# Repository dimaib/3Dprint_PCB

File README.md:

# 3D printer Dual
## Description
A board for controlling all parts of a dual-extruder 3D printer.
- Allows you to control 6 stepper motors
- Table heating 110-230V
- Chamber heating 110-230V
- Heat control of two extruders
- Connection of various limit switches
- Connecting the LCD display
- Printer management via web interface via TCP/IP
>This board is controlled by [RepRapFirmware](https://reprap.org/wiki/RepRap_Firmware) ([GitHub](https://github.com/reprappro/RepRapFirmware))

RepRapFirmware has been optimized and redesigned for the STM32F407VGT controller architecture

## Tools and softwire
- The printed circuit board and circuit diagram of the device are created in [KiCad](https://www.kicad.org/)
- 3D models for PCB components were created in SOLIDWORKS
- Firmware edit in [Atollic TrueSTUDIO for STM32](https://www.st.com/en/development-tools/truestudio.html) in C languages
## Main view PCB

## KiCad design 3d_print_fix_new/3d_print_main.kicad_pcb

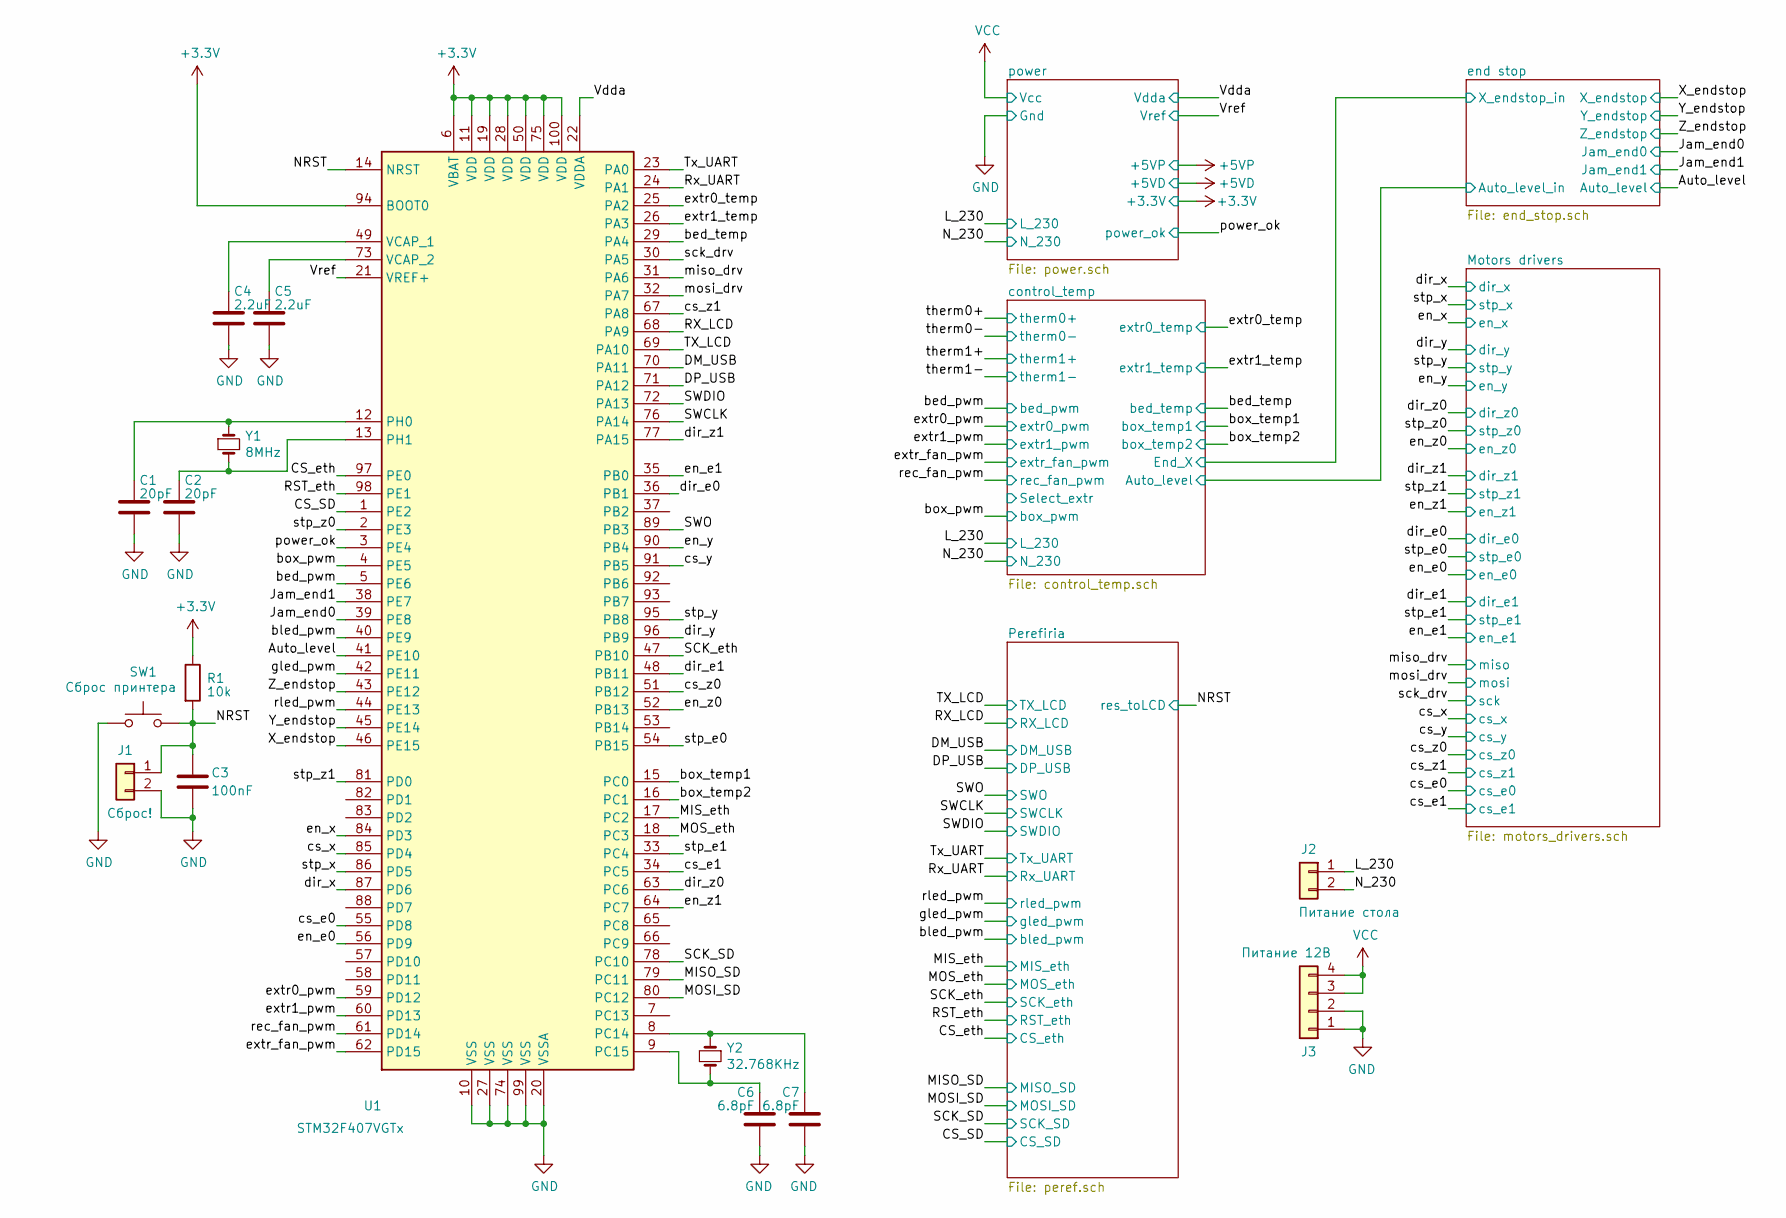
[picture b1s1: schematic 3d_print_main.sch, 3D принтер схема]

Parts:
C1, C2: 20pF; C_0603_1608Metric
C3: 100nF; C_0603_1608Metric
C4, C5: 2.2uF; C_0603_1608Metric
C6, C7: 6.8pF; C_0603_1608Metric
J1: Сброс!; PhoenixContact_MCV_1,5_2-G-3.5_1x02_P3.50mm_Vertical
J2: Питание стола; PhoenixContact_MCV_1,5_2-G-3.5_1x02_P3.50mm_Vertical
J3: Питание 12В; PhoenixContact_MCV_1,5_4-G-3.5_1x04_P3.50mm_Vertical
R1: 10k; R_0603_1608Metric
SW1: Сброс принтера; SW_SPST_PTS645
U1: STM32F407VGTx; LQFP-100_14x14mm_P0.5mm
Y1: 8MHz; Crystal_SMD_5032-2Pin_5.0x3.2mm_HandSoldering
Y2: 32.768KHz; Crystal_SMD_3215-2Pin_3.2x1.5mm

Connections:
/Auto_level: U1.41 (PE10); also elsewhere on the board
/CS_SD: U1.1 (PE2); also elsewhere on the board
/CS_eth: U1.97 (PE0); also elsewhere on the board
/DM_USB: U1.70 (PA11); also elsewhere on the board
/DP_USB: U1.71 (PA12); also elsewhere on the board
/Jam_end0: U1.39 (PE8); also elsewhere on the board
/Jam_end1: U1.38 (PE7); also elsewhere on the board
/L_230: J2.1; also elsewhere on the board
/MISO_SD: U1.79 (PC11); also elsewhere on the board
/MIS_eth: U1.17 (PC2); also elsewhere on the board
/MOSI_SD: U1.80 (PC12); also elsewhere on the board
/MOS_eth: U1.18 (PC3); also elsewhere on the board
/N_230: J2.2; also elsewhere on the board
/RST_eth: U1.98 (PE1); also elsewhere on the board
/RX_LCD: U1.68 (PA9); also elsewhere on the board
/Rx_UART: U1.24 (PA1); also elsewhere on the board
/SCK_SD: U1.78 (PC10); also elsewhere on the board
/SCK_eth: U1.47 (PB10); also elsewhere on the board
/SWCLK: U1.76 (PA14); also elsewhere on the board
/SWDIO: U1.72 (PA13); also elsewhere on the board
/TX_LCD: U1.69 (PA10); also elsewhere on the board
/Tx_UART: U1.23 (PA0); also elsewhere on the board
/Vdda: U1.22 (VDDA); also elsewhere on the board
/Vref: U1.21 (VREF+); also elsewhere on the board
/X_endstop: U1.46 (PE15); also elsewhere on the board
/Y_endstop: U1.45 (PE14); also elsewhere on the board
/Z_endstop: U1.43 (PE12); also elsewhere on the board
/bed_pwm: U1.5 (PE6); also elsewhere on the board
/bed_temp: U1.29 (PA4); also elsewhere on the board
/bled_pwm: U1.40 (PE9); also elsewhere on the board
/box_pwm: U1.4 (PE5); also elsewhere on the board
/box_temp1: U1.15 (PC0); also elsewhere on the board
/box_temp2: U1.16 (PC1); also elsewhere on the board
/cs_e0: U1.55 (PD8); also elsewhere on the board
/cs_e1: U1.34 (PC5); also elsewhere on the board
/cs_x: U1.85 (PD4); also elsewhere on the board
/cs_y: U1.91 (PB5); also elsewhere on the board
/cs_z0: U1.51 (PB12); also elsewhere on the board
/cs_z1: U1.67 (PA8); also elsewhere on the board
/dir_e0: U1.36 (PB1); also elsewhere on the board
/dir_e1: U1.48 (PB11); also elsewhere on the board
/dir_x: U1.87 (PD6); also elsewhere on the board
/dir_y: U1.96 (PB9); also elsewhere on the board
/dir_z0: U1.63 (PC6); also elsewhere on the board
/dir_z1: U1.77 (PA15); also elsewhere on the board
/en_e0: U1.56 (PD9); also elsewhere on the board
/en_e1: U1.35 (PB0); also elsewhere on the board
/en_x: U1.84 (PD3); also elsewhere on the board
/en_y: U1.90 (PB4); also elsewhere on the board
/en_z0: U1.52 (PB13); also elsewhere on the board
/en_z1: U1.64 (PC7); also elsewhere on the board
/extr0_pwm: U1.59 (PD12); also elsewhere on the board
/extr0_temp: U1.25 (PA2); also elsewhere on the board
/extr1_pwm: U1.60 (PD13); also elsewhere on the board
/extr1_temp: U1.26 (PA3); also elsewhere on the board
/extr_fan_pwm: U1.62 (PD15); also elsewhere on the board
/gled_pwm: U1.42 (PE11); also elsewhere on the board
/miso_drv: U1.31 (PA6); also elsewhere on the board
/mosi_drv: U1.32 (PA7); also elsewhere on the board
/power_ok: U1.3 (PE4); also elsewhere on the board
/rec_fan_pwm: U1.61 (PD14); also elsewhere on the board
/rled_pwm: U1.44 (PE13); also elsewhere on the board
/sck_drv: U1.30 (PA5); also elsewhere on the board
/stp_e0: U1.54 (PB15); also elsewhere on the board
/stp_e1: U1.33 (PC4); also elsewhere on the board
/stp_x: U1.86 (PD5); also elsewhere on the board
/stp_y: U1.95 (PB8); also elsewhere on the board
/stp_z0: U1.2 (PE3); also elsewhere on the board
/stp_z1: U1.81 (PD0); also elsewhere on the board
unnamed: C4.1, U1.49 (VCAP_1)
unnamed: C5.1, U1.73 (VCAP_2)
unnamed: C6.1, U1.9 (PC15), Y2.2
unnamed: C7.1, U1.8 (PC14), Y2.1
VCC: J3.3, J3.4; also elsewhere on the board

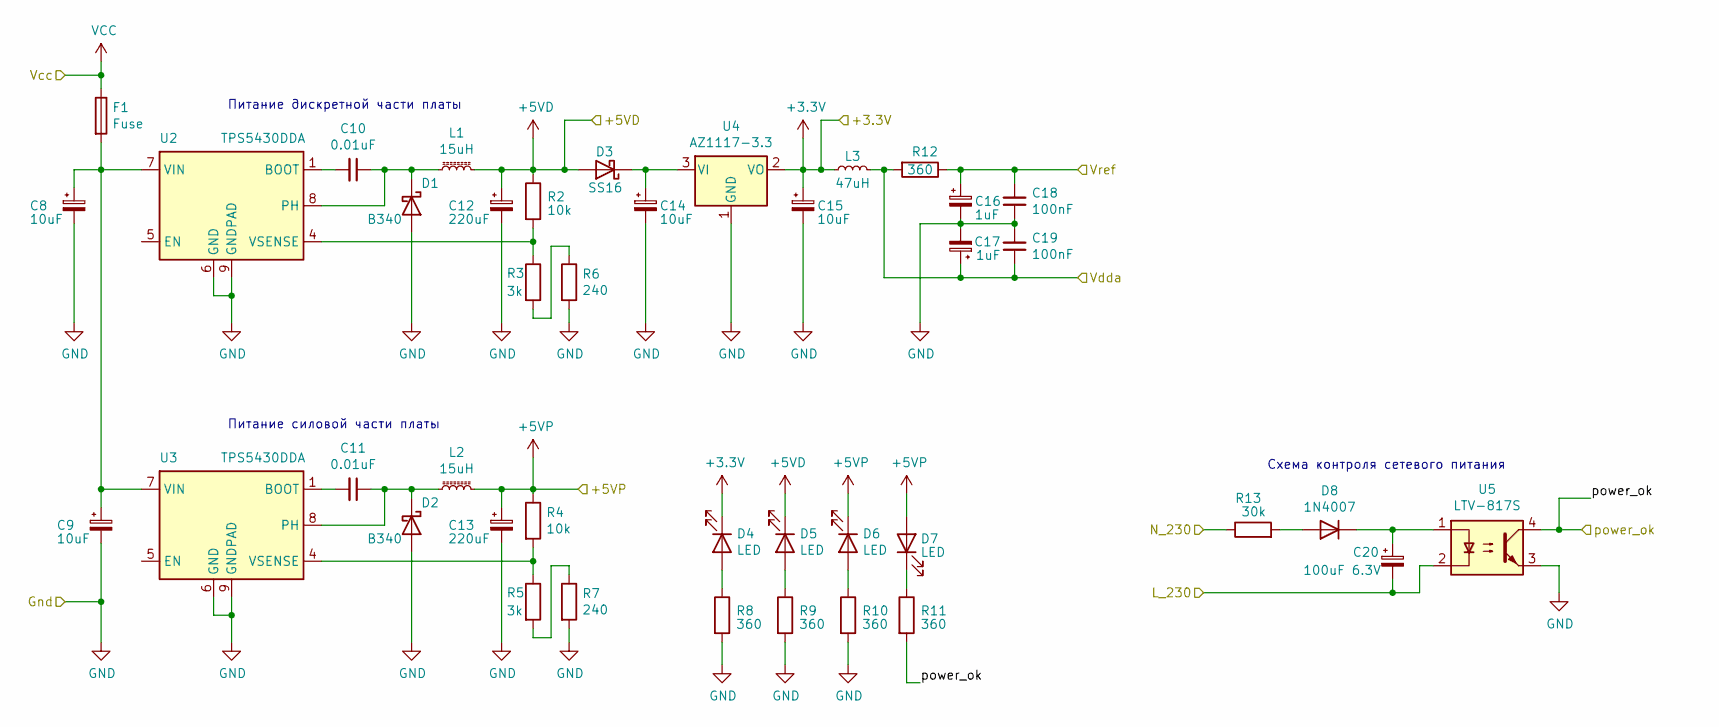
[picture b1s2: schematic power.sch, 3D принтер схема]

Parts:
C8, C9: 10uF; CP_EIA-6032-28_Kemet-C
C10, C11: 0.01uF; C_0603_1608Metric
C12, C13: 220uF; CP_Elec_6.3x7.7
C14, C15: 10uF; CP_EIA-3216-18_Kemet-A
C16, C17: 1uF; CP_EIA-3216-18_Kemet-A
C18, C19: 100nF; C_0603_1608Metric
C20: 100uF 6.3V; CP_EIA-3528-21_Kemet-B
D1, D2: B340; D_SMA
D3: SS16; D_SMA
D4, D5, D6, D7: LED; LED_1206_3216Metric
D8: 1N4007; D_DO-41_SOD81_P7.62mm_Horizontal
F1: Fuse; MF-SM250_Fuse
L1, L2: 15uH; L_10.4x10.4_H4.8
L3: 47uH; L_0805_2012Metric
R2, R4: 10k; R_0603_1608Metric
R3, R5: 3k; R_0603_1608Metric
R6, R7: 240; R_0603_1608Metric
R8, R9, R10, R11, R12: 360; R_0603_1608Metric
R13: 30k; R_2512_6332Metric
U2, U3: TPS5430DDA; TI_SO-PowerPAD-8_ThermalVias
U4: AZ1117-3.3; SOT-223-3_TabPin2
U5: LTV-817S; SMDIP-4_W9.53mm

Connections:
/L_230: C20.2, U5.2; also elsewhere on the board
/N_230: R13.1; also elsewhere on the board
/Vdda: C17.1, C19.1, L3.2, R12.2; also elsewhere on the board
/Vref: C16.1, C18.2, R12.1; also elsewhere on the board
/power_ok: R11.2, U5.4; also elsewhere on the board
unnamed: C8.1, C9.1, F1.2, U2.7 (VIN), U3.7 (VIN)
unnamed: C10.1, D1.1 (K), L1.1, U2.8 (PH)
unnamed: C10.2, U2.1 (BOOT)
unnamed: C11.2, U3.1 (BOOT)
unnamed: C14.1, D3.1 (K), U4.3 (VI)
unnamed: C20.1, D8.2 (K), U5.1
unnamed: D4.2 (A), R8.1
unnamed: D5.2 (A), R9.1
unnamed: D7.1 (K), R11.1
unnamed: D8.1 (A), R13.2
unnamed: R2.2, R3.1, U2.4 (VSENSE)
unnamed: R3.2, R6.1
VCC: F1.1; also elsewhere on the board

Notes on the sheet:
Питание дискретной части платы
Питание силовой части платы
Схема контроля сетевого питания

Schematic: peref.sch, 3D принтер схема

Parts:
C1, C2: 10uF; C_0603_1608Metric
C3, C22, C23: 1uF; C_0603_1608Metric
C21: 10uF; CP_EIA-3216-18_Kemet-A
D2, D9: BAS321; D_SOD-323_HandSoldering
D6: Зелёный; LED_0603_1608Metric_Castellated
D10: SP0503; SOT-143
D11: w5500_module
J4, J5, J7, J12, J14, J16, J18, J20, J21: Conn_01x01; PinHeader_1x01_P2.54mm_Vertical
J6, J8, J11, J13, J15, J17, J19, J45, J46: Conn_01x01; MountingHole_3.2mm_M3_Pad_Via
J9: На монитор; IDC-Header_2x04_P2.54mm_Vertical
J10: LMT01 датчик т; PinHeader_1x01_P2.54mm_Vertical
J22: ST-Link; ZH_Conn_04x01
J23: USB_B_Mini; USB_Micro-B_Molex-105017-0001
J25: Подключение RGB ленты; PhoenixContact_MCV_1,5_3-G-3.5_1x03_P3.50mm_Vertical
Q1: BC817; SOT-23
Q2, Q3: IRLML2060; SOT-23
R4, R15, R18, R19, R20, R25, R26, R59, R60, R61: 10k; R_0603_1608Metric
R5, R7: 50k; R_0603_1608Metric
R10: 150k; R_0603_1608Metric
R14: 360; R_0603_1608Metric
R16, R17: 22; R_0603_1608Metric
R22, R23: 100; R_0603_1608Metric
SW1: Сброс принтера; SW_SPST_PTS645
SW2: Сброс по UART; SW_DIP_SPSTx01_Piano_10.8x4.1mm_W7.62mm_P2.54mm
U3, U11: 74LVC2G14; SOT-23-6
U6: USBLC6-2SC6; SOT-23-6
U7: MicroSD_SPI_CD; GCT-MEM2055-00-190-01-A
U8: CP2102N; QFN-28-1EP_5x5mm_P0.5mm_EP3.35x3.35mm
U12: TPS73018DBV; SOT-23-5

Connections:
/CS_SD: U7.2 (~CS); also elsewhere on the board
/CS_eth: D11.5 (SCN); also elsewhere on the board
/DM_USB: R17.1; also elsewhere on the board
/DP_USB: R16.1; also elsewhere on the board
/MISO_SD: U7.7 (DO); also elsewhere on the board
/MIS_eth: D11.7 (MISO); also elsewhere on the board
/MOSI_SD: U7.3 (DI); also elsewhere on the board
/MOS_eth: D11.3 (MOSI); also elsewhere on the board
/Perefiria/blue_led: J25.4; also elsewhere on the board
/Perefiria/green_led: J25.3, Q3.3 (D), R26.2
/Perefiria/red_led: J25.2, Q2.3 (D), R25.2
/RST_eth: D11.8 (RST); also elsewhere on the board
/RX_LCD: J9.6; also elsewhere on the board
/Rx_UART: U8.26 (TXD); also elsewhere on the board
/SCK_SD: U7.5 (SCLK); also elsewhere on the board
/SCK_eth: D11.4 (SCK); also elsewhere on the board
/SWCLK: J22.3; also elsewhere on the board
/SWDIO: J22.5; also elsewhere on the board
/TX_LCD: J9.8; also elsewhere on the board
/Tx_UART: U8.25 (RXD); also elsewhere on the board
/gled_pwm: R20.1, R23.2; also elsewhere on the board
/rled_pwm: R19.1, R22.2; also elsewhere on the board
unnamed 86: C23.1; also elsewhere on the board
unnamed: C23.2, U8.28 (~DTR)
unnamed: D9.1 (A), J23.1 (VBUS)
unnamed: D10.3 (K), J23.2 (D-), U8.5 (D-)
unnamed: D10.4 (K), J23.3 (D+), U8.4 (D+)
unnamed: J9.2, U6.1 (IO1)
unnamed: J9.4, U6.3 (IO2)
unnamed: J9.10, R14.1
unnamed: Q1.1 (B), R14.2, R15.1
unnamed: Q2.1 (G), R22.1
unnamed: Q3.1 (G), R23.1
unnamed: R16.2, U6.6 (IO1)
unnamed: R17.2, U6.4 (IO2)
unnamed: R18.2, U8.9 (~RSTb)
unnamed: R59.1, R60.1
VCC: J25.1, R25.1, R26.1; also elsewhere on the board

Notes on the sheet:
USB-UART debug
Защита USB от ЭМП
Для осциллографа
Отверстия для крепежа M3
Схема сброса

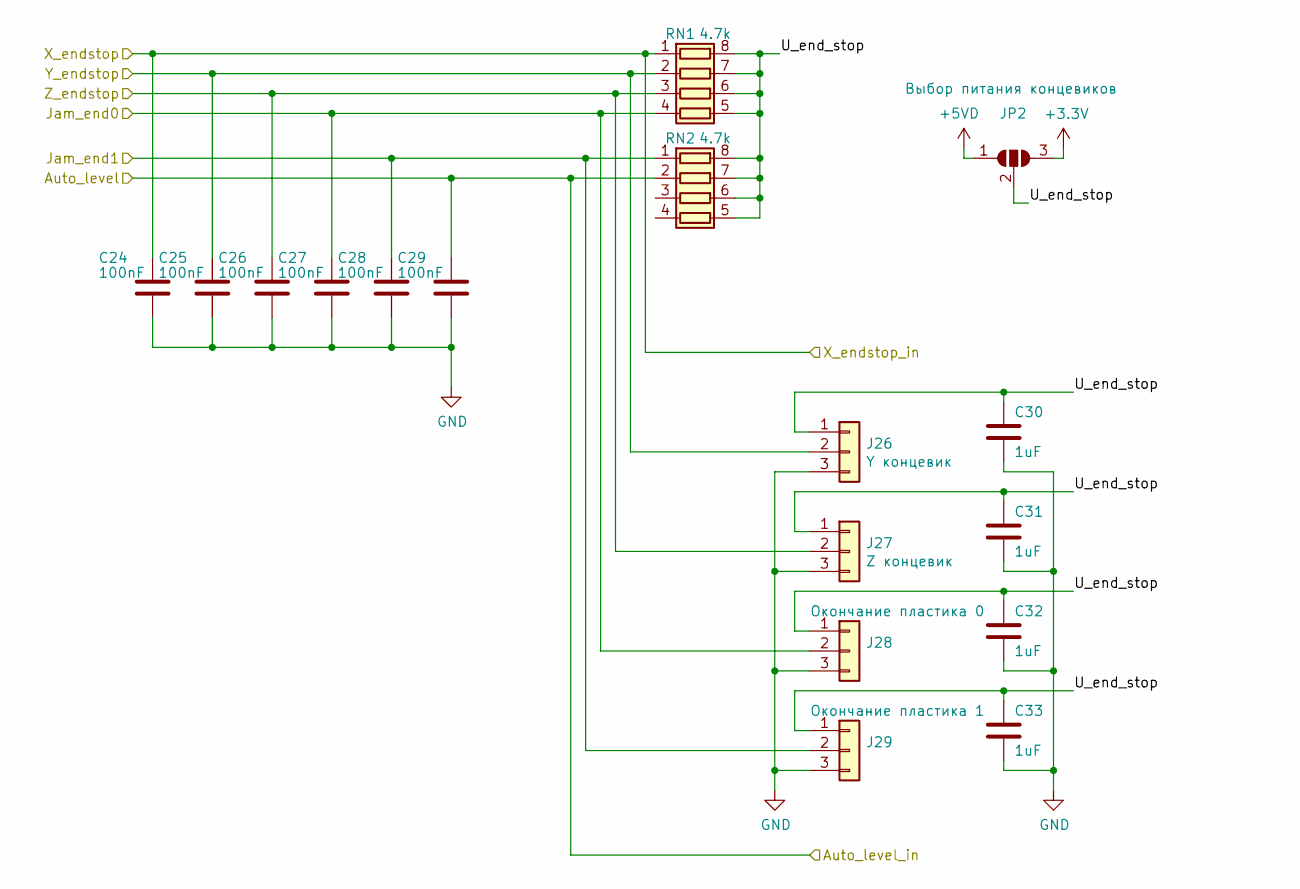
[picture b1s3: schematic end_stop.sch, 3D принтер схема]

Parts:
C24, C25, C26, C27, C28, C29: 100nF; C_0603_1608Metric
C30, C31, C32, C33: 1uF; C_0603_1608Metric
J26: Y концевик; PhoenixContact_MCV_1,5_3-G-3.5_1x03_P3.50mm_Vertical
J27: Z концевик; PhoenixContact_MCV_1,5_3-G-3.5_1x03_P3.50mm_Vertical
J28: Окончание пластика 0; PhoenixContact_MCV_1,5_3-G-3.5_1x03_P3.50mm_Vertical
J29: Окончание пластика 1; PhoenixContact_MCV_1,5_3-G-3.5_1x03_P3.50mm_Vertical
JP2: Выбор питания концевиков; SolderJumper-3_P1.3mm_Bridged2Bar12_RoundedPad1.0x1.5mm_Num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
RN1, RN2: 4.7k; R_Array_Convex_4x0603

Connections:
/Auto_level: C29.1, RN2.2 (R2.1); also elsewhere on the board
/Jam_end0: C27.1, J28.2, RN1.4 (R4.1); also elsewhere on the board
/Jam_end1: C28.1, J29.2, RN2.1 (R1.1); also elsewhere on the board
/X_endstop: C24.1, RN1.1 (R1.1); also elsewhere on the board
/Y_endstop: C25.1, J26.2, RN1.2 (R2.1); also elsewhere on the board
/Z_endstop: C26.1, J27.2, RN1.3 (R3.1); also elsewhere on the board
/end stop/U_end_stop: C30.1, C31.1, C32.1, C33.1, J26.1, J27.1, J28.1, J29.1, JP2.2 (C), RN1.5 (R4.2), RN1.6 (R3.2), RN1.7 (R2.2), RN1.8 (R1.2), RN2.5 (R4.2), RN2.6 (R3.2), RN2.7 (R2.2), RN2.8 (R1.2)

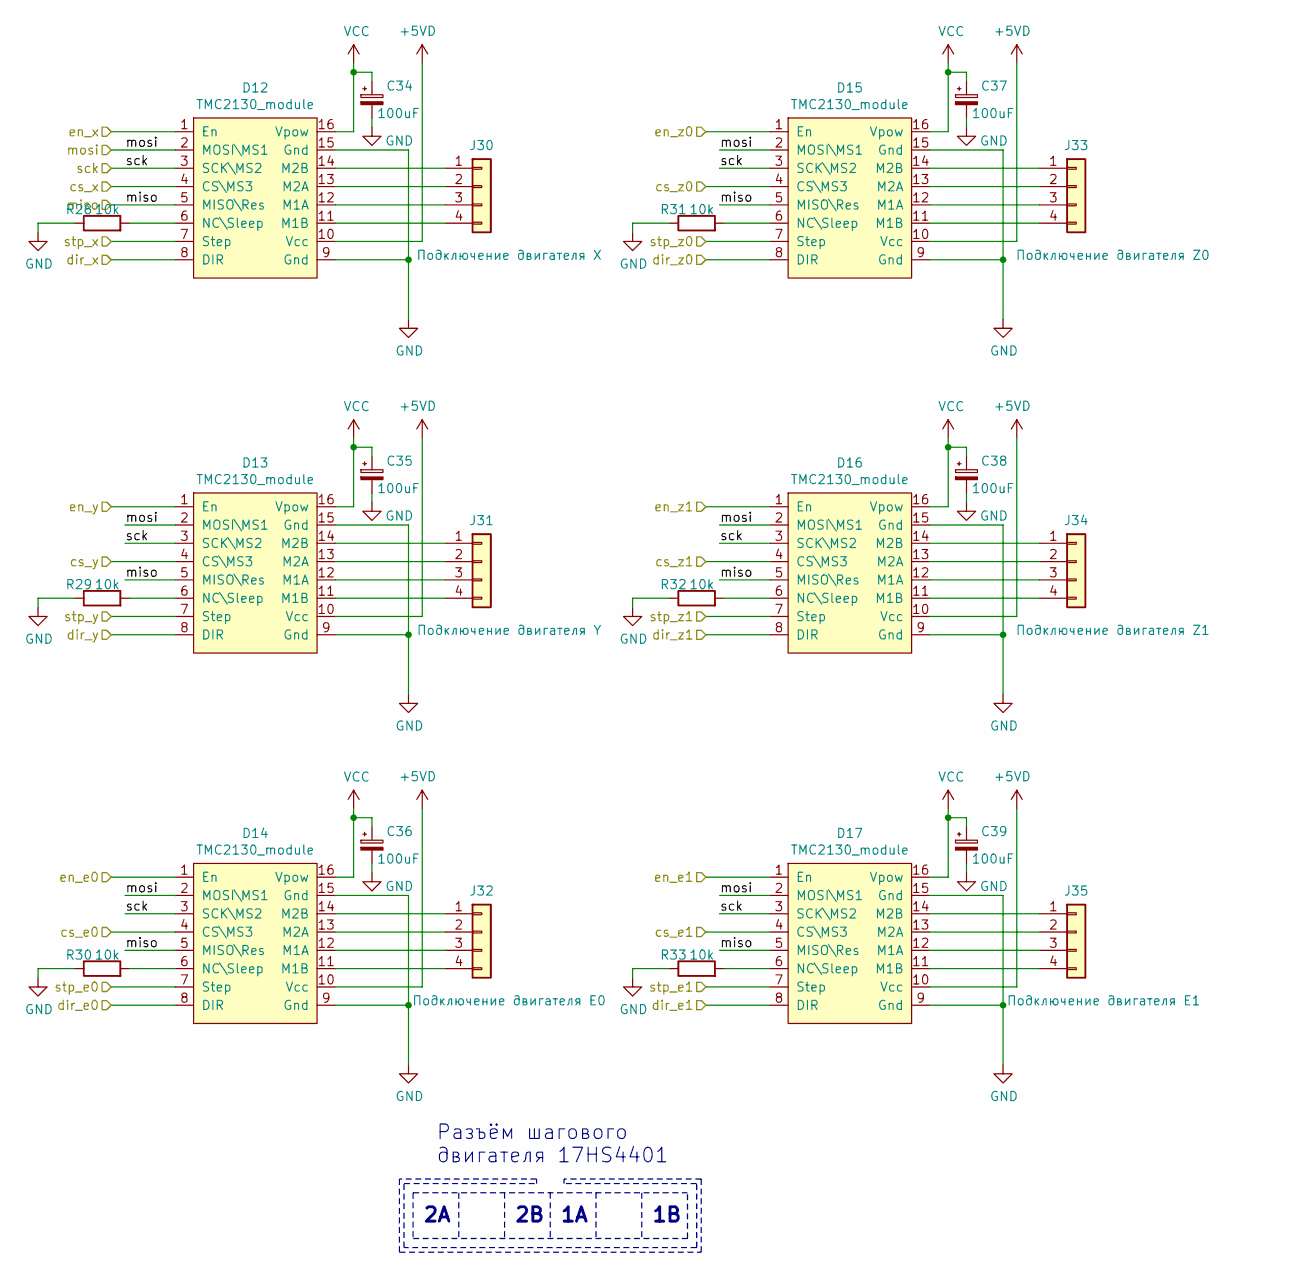
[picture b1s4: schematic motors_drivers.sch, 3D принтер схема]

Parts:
C34, C35, C36, C37, C38, C39: 100uF; CP_Elec_6.3x7.7
D12, D13, D14, D15, D16, D17: TMC2130_module; TMC2130_Module
J30: Подключение двигателя X; PhoenixContact_MCV_1,5_4-G-3.5_1x04_P3.50mm_Vertical
J31: Подключение двигателя Y; PhoenixContact_MCV_1,5_4-G-3.5_1x04_P3.50mm_Vertical
J32: Подключение двигателя E0; PhoenixContact_MCV_1,5_4-G-3.5_1x04_P3.50mm_Vertical
J33: Подключение двигателя Z0; PhoenixContact_MCV_1,5_4-G-3.5_1x04_P3.50mm_Vertical
J34: Подключение двигателя Z1; PhoenixContact_MCV_1,5_4-G-3.5_1x04_P3.50mm_Vertical
J35: Подключение двигателя E1; PhoenixContact_MCV_1,5_4-G-3.5_1x04_P3.50mm_Vertical
R28, R29, R30, R31, R32, R33: 10k; R_0603_1608Metric

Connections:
/cs_e0: D14.4 (CS\MS3); also elsewhere on the board
/cs_e1: D17.4 (CS\MS3); also elsewhere on the board
/cs_x: D12.4 (CS\MS3); also elsewhere on the board
/cs_y: D13.4 (CS\MS3); also elsewhere on the board
/cs_z0: D15.4 (CS\MS3); also elsewhere on the board
/cs_z1: D16.4 (CS\MS3); also elsewhere on the board
/dir_e0: D14.8 (DIR); also elsewhere on the board
/dir_e1: D17.8 (DIR); also elsewhere on the board
/dir_x: D12.8 (DIR); also elsewhere on the board
/dir_y: D13.8 (DIR); also elsewhere on the board
/dir_z0: D15.8 (DIR); also elsewhere on the board
/dir_z1: D16.8 (DIR); also elsewhere on the board
/en_e0: D14.1 (En); also elsewhere on the board
/en_e1: D17.1 (En); also elsewhere on the board
/en_x: D12.1 (En); also elsewhere on the board
/en_y: D13.1 (En); also elsewhere on the board
/en_z0: D15.1 (En); also elsewhere on the board
/en_z1: D16.1 (En); also elsewhere on the board
/miso_drv: D12.5 (MISO\Res), D13.5 (MISO\Res), D14.5 (MISO\Res), D15.5 (MISO\Res), D16.5 (MISO\Res), D17.5 (MISO\Res); also elsewhere on the board
/mosi_drv: D12.2 (MOSI\MS1), D13.2 (MOSI\MS1), D14.2 (MOSI\MS1), D15.2 (MOSI\MS1), D16.2 (MOSI\MS1), D17.2 (MOSI\MS1); also elsewhere on the board
/sck_drv: D12.3 (SCK\MS2), D13.3 (SCK\MS2), D14.3 (SCK\MS2), D15.3 (SCK\MS2), D16.3 (SCK\MS2), D17.3 (SCK\MS2); also elsewhere on the board
/stp_e0: D14.7 (Step); also elsewhere on the board
/stp_e1: D17.7 (Step); also elsewhere on the board
/stp_x: D12.7 (Step); also elsewhere on the board
/stp_y: D13.7 (Step); also elsewhere on the board
/stp_z0: D15.7 (Step); also elsewhere on the board
/stp_z1: D16.7 (Step); also elsewhere on the board
unnamed: D12.6 (NC\Sleep), R28.2
unnamed: D12.11 (M1B), J30.4
unnamed: D12.12 (M1A), J30.3
unnamed: D12.13 (M2A), J30.2
unnamed: D12.14 (M2B), J30.1
unnamed: D13.6 (NC\Sleep), R29.2
unnamed: D13.11 (M1B), J31.4
unnamed: D13.12 (M1A), J31.3
unnamed: D13.13 (M2A), J31.2
unnamed: D13.14 (M2B), J31.1
unnamed: D14.6 (NC\Sleep), R30.2
unnamed: D14.11 (M1B), J32.4
unnamed: D14.12 (M1A), J32.3
unnamed: D14.13 (M2A), J32.2
unnamed: D14.14 (M2B), J32.1
unnamed: D15.6 (NC\Sleep), R31.2
unnamed: D15.11 (M1B), J33.4
unnamed: D15.12 (M1A), J33.3
unnamed: D15.13 (M2A), J33.2
unnamed: D15.14 (M2B), J33.1
unnamed: D16.6 (NC\Sleep), R32.2
unnamed: D16.11 (M1B), J34.4
unnamed: D16.12 (M1A), J34.3
unnamed: D16.13 (M2A), J34.2
unnamed: D16.14 (M2B), J34.1
unnamed: D17.6 (NC\Sleep), R33.2
unnamed: D17.11 (M1B), J35.4
unnamed: D17.12 (M1A), J35.3
unnamed: D17.13 (M2A), J35.2
unnamed: D17.14 (M2B), J35.1
VCC: C34.1, C35.1, C36.1, C37.1, C38.1, C39.1, D12.16 (Vpow), D13.16 (Vpow), D14.16 (Vpow), D15.16 (Vpow), D16.16 (Vpow), D17.16 (Vpow); also elsewhere on the board

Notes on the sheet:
Разъём шагового двигателя 17HS4401

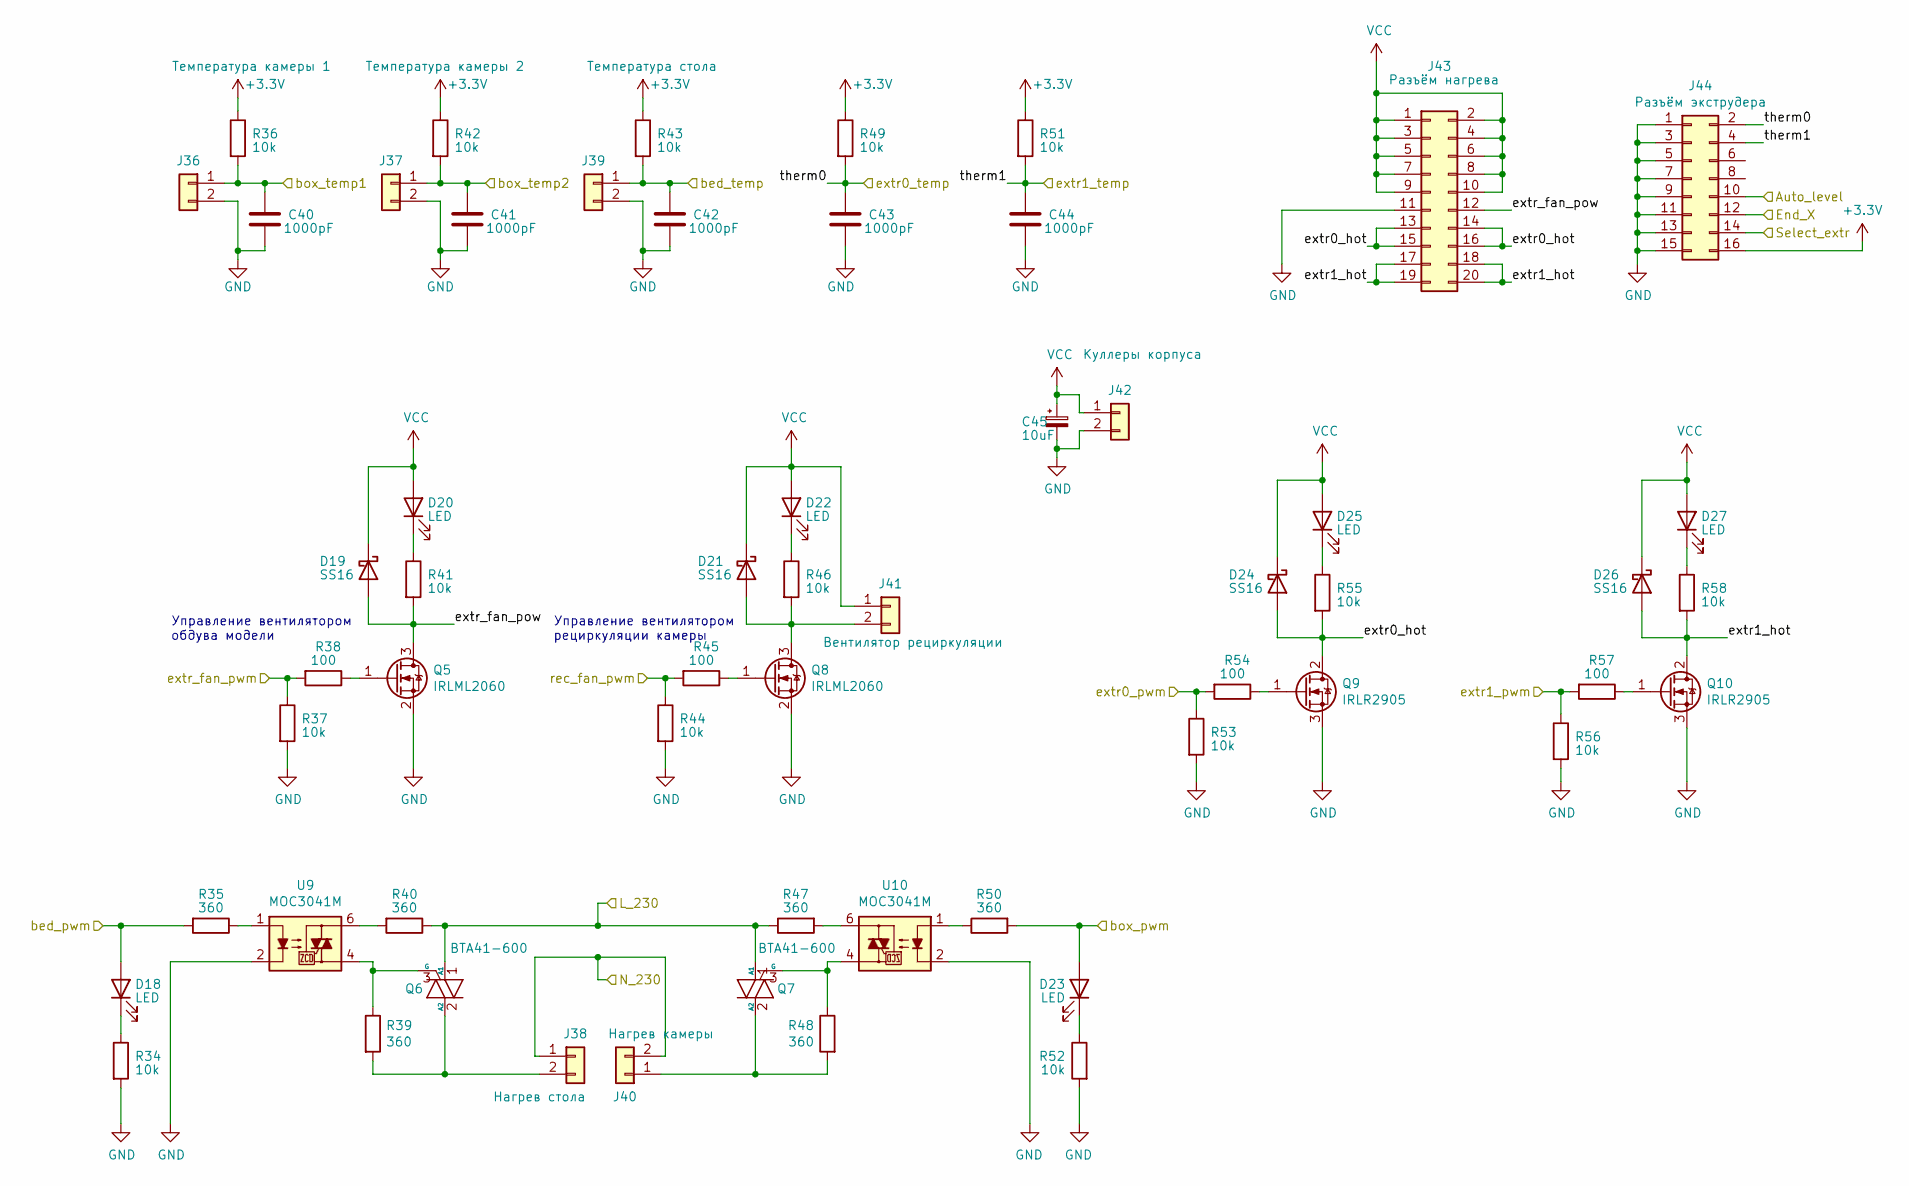
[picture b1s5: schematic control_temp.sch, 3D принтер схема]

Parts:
C40, C41, C42, C43, C44: 1000pF; C_0603_1608Metric
C45: 10uF; CP_EIA-6032-28_Kemet-C
D18, D20, D22, D23, D25, D27: LED; LED_1206_3216Metric
D19, D21, D24, D26: SS16; D_SMA
J36: Температура камеры 1; PhoenixContact_MCV_1,5_2-G-3.5_1x02_P3.50mm_Vertical
J37: Температура камеры 2; PhoenixContact_MCV_1,5_2-G-3.5_1x02_P3.50mm_Vertical
J38: Нагрев стола; PhoenixContact_MCV_1,5_2-G-3.5_1x02_P3.50mm_Vertical
J39: Температура стола; PhoenixContact_MCV_1,5_2-G-3.5_1x02_P3.50mm_Vertical
J40: Нагрев камеры; PhoenixContact_MCV_1,5_2-G-3.5_1x02_P3.50mm_Vertical
J41: Вентилятор рециркуляции; PhoenixContact_MCV_1,5_2-G-3.5_1x02_P3.50mm_Vertical
J42: Куллеры корпуса; PhoenixContact_MCV_1,5_2-G-3.5_1x02_P3.50mm_Vertical
J43: Разъём нагрева; IDC-Header_2x10_P2.54mm_Vertical
J44: Разъём экструдера; IDC-Header_2x08_P2.54mm_Vertical
Q5, Q8: IRLML2060; SOT-23
Q6, Q7: BTA41-600; TOP3
Q9, Q10: IRLR2905; TO-252-2
R34, R36, R37, R41, R42, R43, R44, R46, R49, R51, R52, R53, R55, R56, R58: 10k; R_0603_1608Metric
R35, R50: 360; R_0603_1608Metric
R38, R45, R54, R57: 100; R_0603_1608Metric
R39, R40, R47, R48: 360; R_1206_3216Metric
U9, U10: MOC3041M; DIP-6_W7.62mm

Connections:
/Auto_level: J44.10; also elsewhere on the board
/L_230: Q6.1 (A1), Q7.1 (A1), R40.1, R47.1; also elsewhere on the board
/N_230: J38.1, J40.2; also elsewhere on the board
/X_endstop: J44.12; also elsewhere on the board
/bed_pwm: D18.2 (A), R35.2; also elsewhere on the board
/bed_temp: C42.1, J39.1, R43.2; also elsewhere on the board
/box_pwm: D23.2 (A), R50.2; also elsewhere on the board
/box_temp1: C40.1, J36.1, R36.2; also elsewhere on the board
/box_temp2: C41.1, J37.1, R42.2; also elsewhere on the board
/control_temp/extr0_hot: D24.2 (A), J43.13, J43.14, J43.15, J43.16, Q9.2 (D), R55.2
/control_temp/extr1_hot: D26.2 (A), J43.17, J43.18, J43.19, J43.20, Q10.2 (D), R58.2
/control_temp/extr_fan_pow: D19.2 (A), J43.12, Q5.3 (D), R41.2
/extr0_pwm: R53.1, R54.2; also elsewhere on the board
/extr0_temp: C43.1, J44.2, R49.2; also elsewhere on the board
/extr1_pwm: R56.1, R57.2; also elsewhere on the board
/extr1_temp: C44.1, J44.4, R51.2; also elsewhere on the board
/extr_fan_pwm: R37.1, R38.2; also elsewhere on the board
/rec_fan_pwm: R44.1, R45.2; also elsewhere on the board
unnamed: D18.1 (K), R34.1
unnamed: D20.1 (K), R41.1
unnamed: D21.2 (A), J41.2, Q8.3 (D), R46.2
unnamed: D22.1 (K), R46.1
unnamed: D23.1 (K), R52.1
unnamed: D25.1 (K), R55.1
unnamed: D27.1 (K), R58.1
unnamed: J38.2, Q6.2 (A2), R39.2
unnamed: J40.1, Q7.2 (A2), R48.2
unnamed: Q5.1 (G), R38.1
unnamed: Q6.3 (G), R39.1, U9.4
unnamed: Q7.3 (G), R48.1, U10.4
unnamed: Q8.1 (G), R45.1
unnamed: Q9.1 (G), R54.1
unnamed: Q10.1 (G), R57.1
unnamed: R35.1, U9.1
unnamed: R40.2, U9.6
unnamed: R47.2, U10.6
unnamed: R50.1, U10.1
VCC: C45.1, D19.1 (K), D20.2 (A), D21.1 (K), D22.2 (A), D24.1 (K), D25.2 (A), D26.1 (K), D27.2 (A), J41.1, J42.1, J43.1, J43.2, J43.3, J43.4, J43.5, J43.6, J43.7, J43.8, J43.9, J43.10; also elsewhere on the board

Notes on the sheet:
Управление вентилятором обдува модели
Управление вентилятором рециркуляции камеры

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
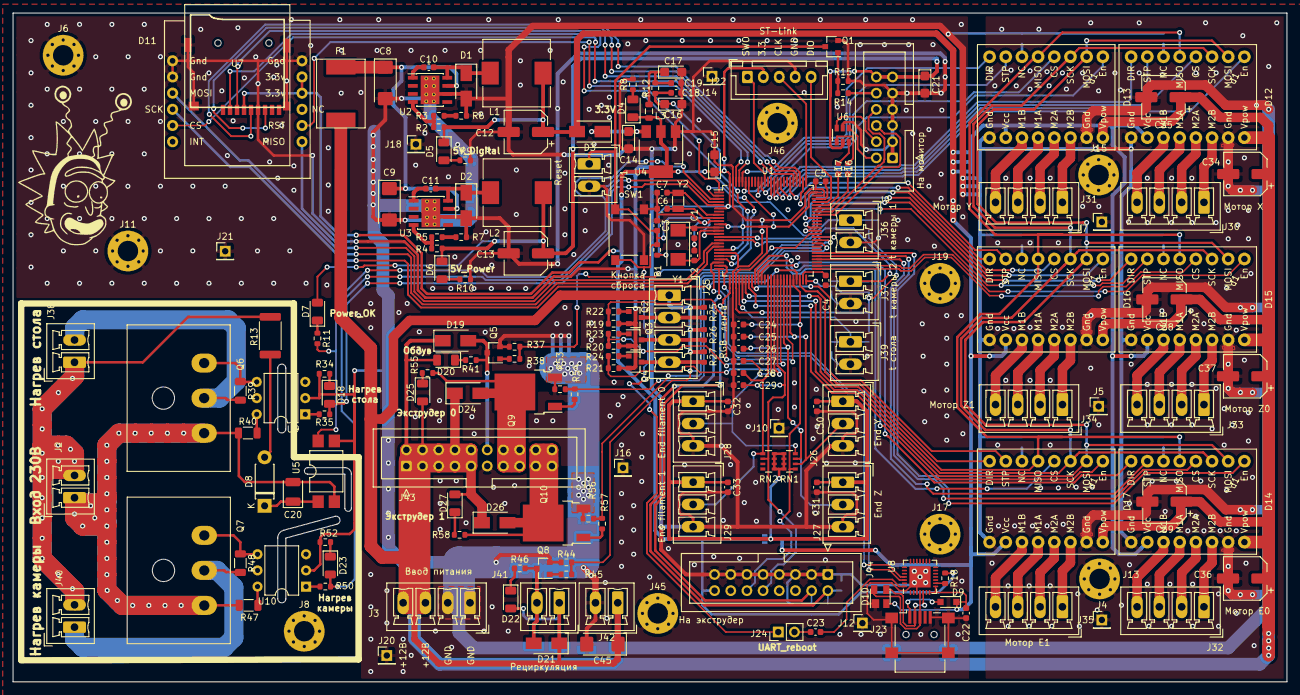
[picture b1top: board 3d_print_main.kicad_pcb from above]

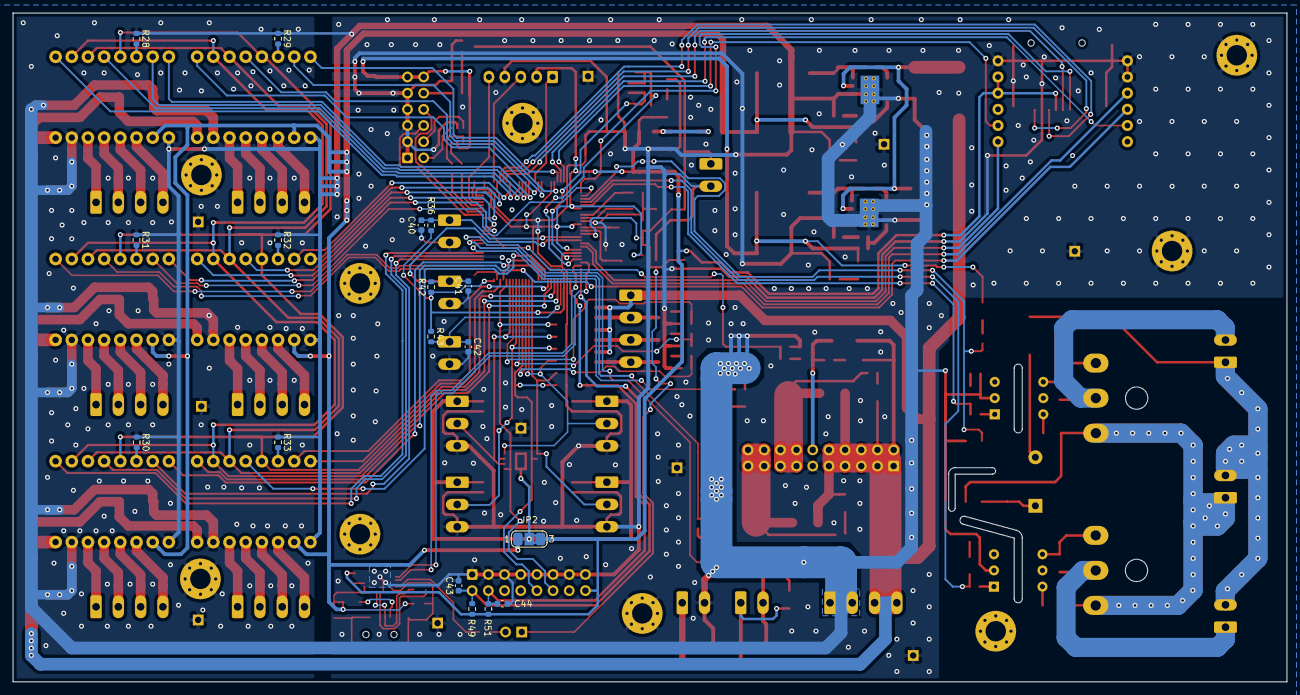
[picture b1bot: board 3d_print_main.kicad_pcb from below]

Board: 2 copper layers, 200.0 x 105.0 mm, 206 parts (17 on the bottom side), 169 nets.

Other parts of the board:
J24: Джампер сброса; PinHeader_1x02_P2.54mm_Vertical
Q4: IRLML2060; SOT-23
R21, R27: 10k; R_0603_1608Metric
R24: 100; R_0603_1608Metric

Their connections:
/Perefiria/blue_led: Q4.3, R27.2; also elsewhere on the board
/bled_pwm: R21.1, R24.2; also elsewhere on the board
unnamed 86: J24.2; also elsewhere on the board
unnamed: Q4.1, R24.1
VCC: R27.1; also elsewhere on the board

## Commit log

2022-04-24 add screen
2022-04-24 add readme
